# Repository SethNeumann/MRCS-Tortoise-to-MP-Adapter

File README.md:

# REPO NAME: MRCS-Tortoise-to-MP-Adapter

## License: Creative Commons Attribution-NonCommercial-ShareAlike

relay driven by a low power tortoise drive circuit (usually an LM324). Relay operates and switches 12V to MP Motor
eventually will have a 3.5mm phoenix plug for MP10

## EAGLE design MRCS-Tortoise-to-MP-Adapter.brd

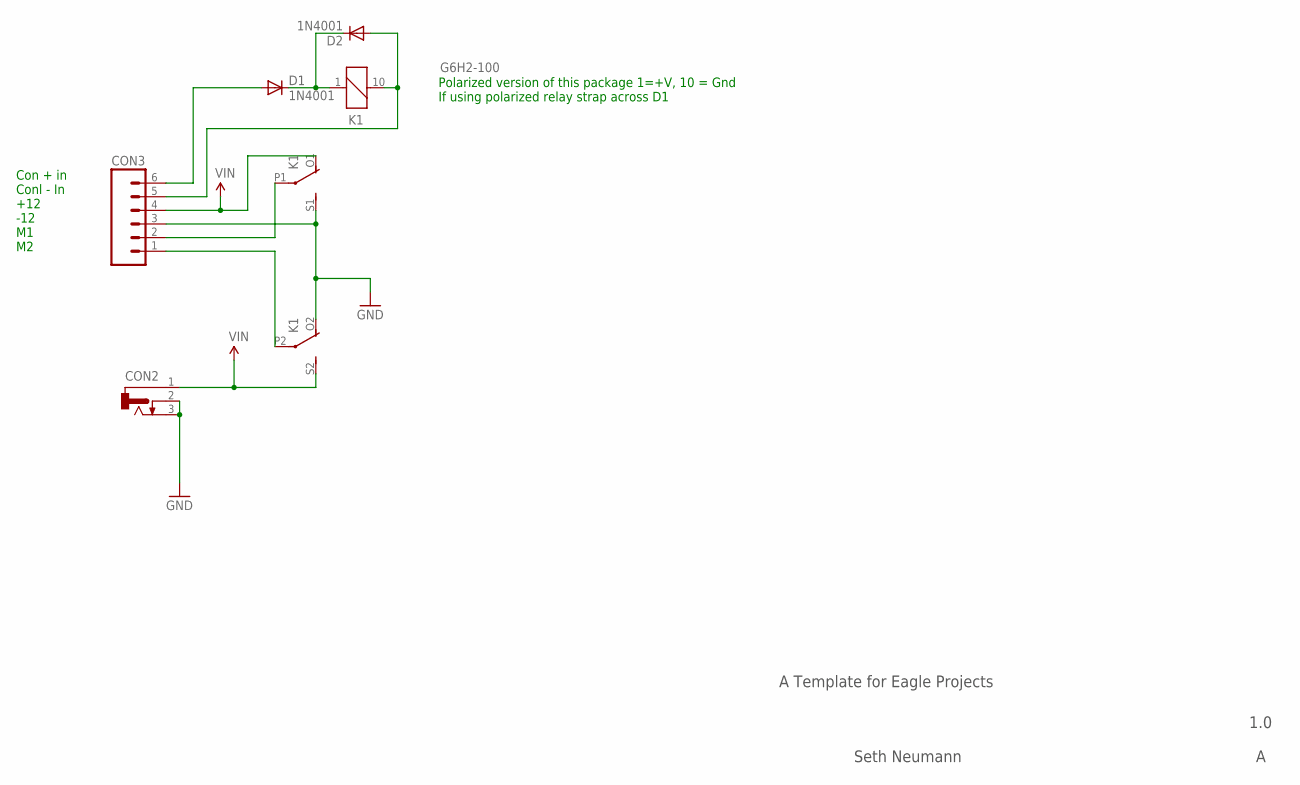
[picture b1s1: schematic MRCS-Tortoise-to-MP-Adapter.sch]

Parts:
CON2: CONNECTOR-DC-POWER-RA; DCJ0202
CON3: CONNECTOR-M063.5MM-6; SCREWTERMINAL-3.5MM-6
D1, D2: 1N4001; DIODE-1N4001
K1: G6H2-100

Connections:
GND: CON2.2, CON2.3, CON3.3, K1.O2 (O), K1.S1 (S)
unnamed: CON3.6, D1.A
unnamed: D1.C, D2.C, K1.1
unnamed: CON3.5, D2.A, K1.10 (2)
unnamed: CON3.2, K1.P1
unnamed: CON3.1, K1.P2
VIN: CON2.1, CON3.4, K1.O1 (O), K1.S2 (S)

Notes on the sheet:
A Template for Eagle Projects
1.0
Seth Neumann
Polarized version of this package 1=+V, 10 = Gnd If using polarized relay strap across D1
Con + in Conl - In +12 -12 M1 M2

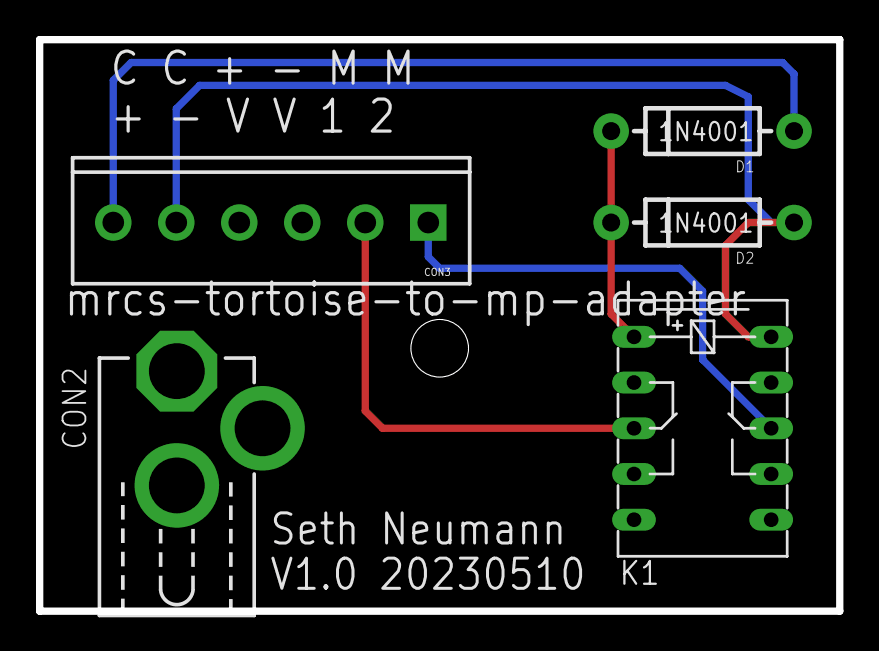
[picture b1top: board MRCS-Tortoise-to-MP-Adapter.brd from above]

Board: 2 copper layers, 44.5 x 31.8 mm, 8 parts (0 on the bottom side), 7 nets.

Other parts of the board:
U$1: MRCSLOGOTOP
U$2: CA-PROP65WARNING
U$3: MRCSLOGOBTM

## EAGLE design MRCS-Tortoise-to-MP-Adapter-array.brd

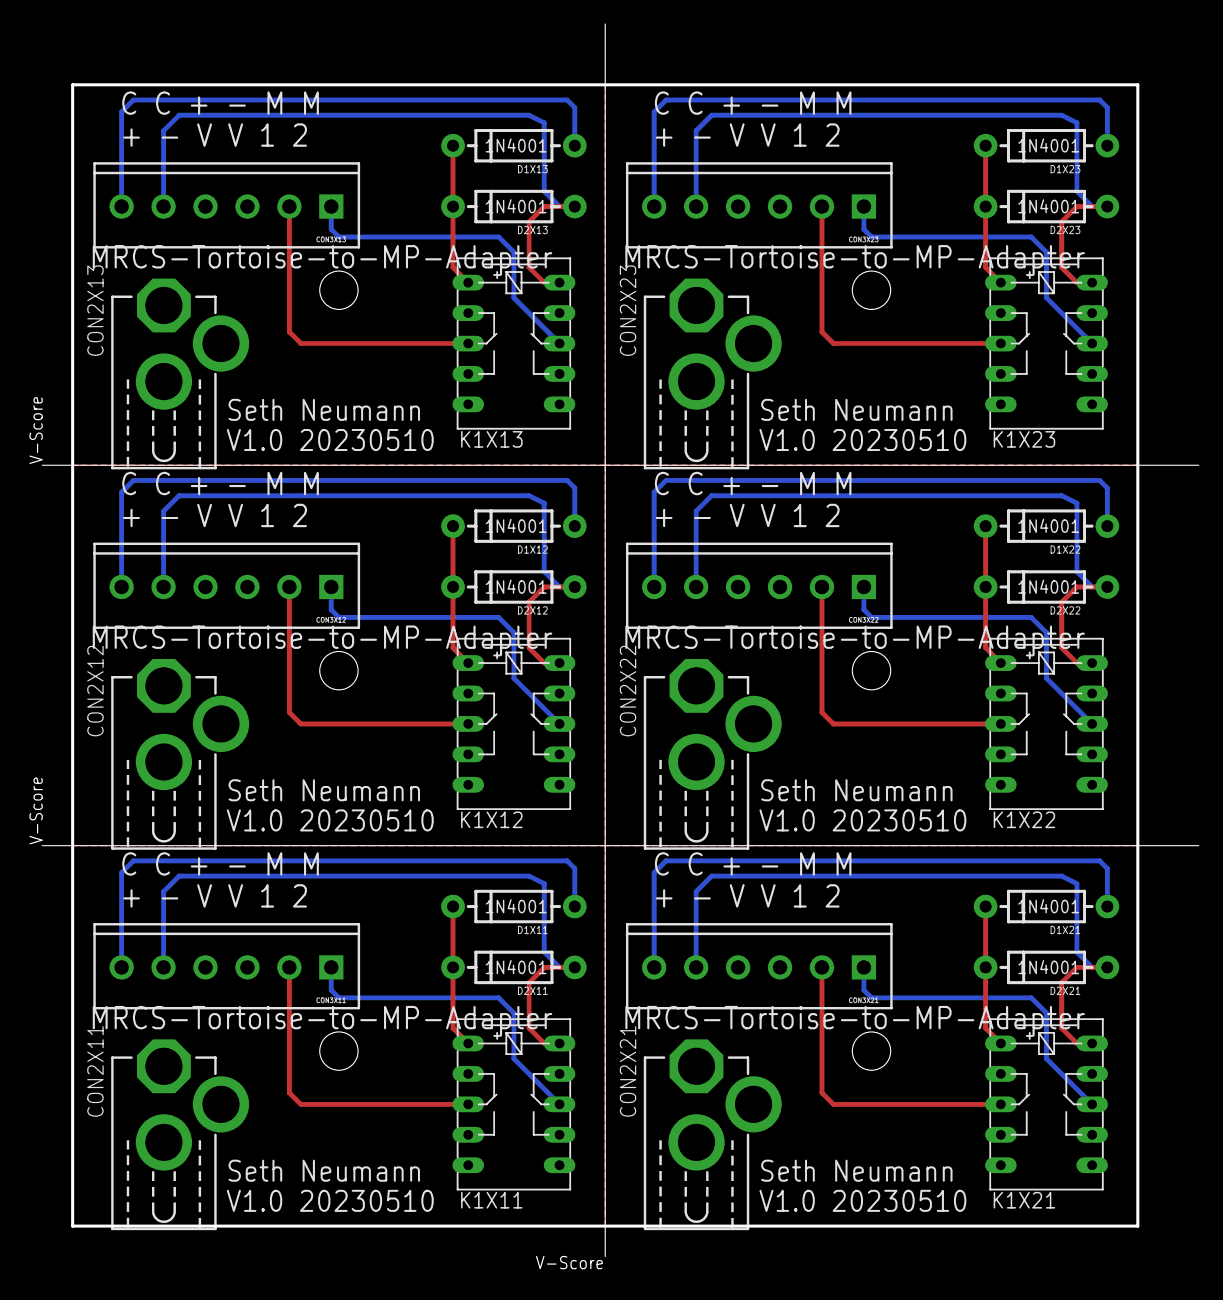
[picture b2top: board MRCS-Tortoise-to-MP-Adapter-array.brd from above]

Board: 2 copper layers, 97.8 x 104.2 mm, 48 parts (0 on the bottom side), 42 nets.

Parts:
CON2X11, CON2X12, CON2X13, CON2X21, CON2X22, CON2X23: DCJ0202
CON3X11, CON3X12, CON3X13, CON3X21, CON3X22, CON3X23: SCREWTERMINAL-3.5MM-6
D1X11, D1X12, D1X13, D1X21, D1X22, D1X23, D2X11, D2X12, D2X13, D2X21, D2X22, D2X23: 1N4001; DIODE-1N4001
K1X11, K1X12, K1X13, K1X21, K1X22, K1X23: G6H2-100
U$1X11, U$1X12, U$1X13, U$1X21, U$1X22, U$1X23: MRCSLOGOTOP
U$2X11, U$2X12, U$2X13, U$2X21, U$2X22, U$2X23: CA-PROP65WARNING
U$3X11, U$3X12, U$3X13, U$3X21, U$3X22, U$3X23: MRCSLOGOBTM

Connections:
GNDX11: CON2X11.2, CON2X11.3, CON3X11.3, K1X11.O2, K1X11.S1
GNDX12: CON2X12.2, CON2X12.3, CON3X12.3, K1X12.O2, K1X12.S1
GNDX13: CON2X13.2, CON2X13.3, CON3X13.3, K1X13.O2, K1X13.S1
GNDX21: CON2X21.2, CON2X21.3, CON3X21.3, K1X21.O2, K1X21.S1
GNDX22: CON2X22.2, CON2X22.3, CON3X22.3, K1X22.O2, K1X22.S1
GNDX23: CON2X23.2, CON2X23.3, CON3X23.3, K1X23.O2, K1X23.S1
unnamed: CON3X11.6, D1X11.A
unnamed: CON3X12.6, D1X12.A
unnamed: CON3X13.6, D1X13.A
unnamed: CON3X21.6, D1X21.A
unnamed: CON3X22.6, D1X22.A
unnamed: CON3X23.6, D1X23.A
unnamed: D1X11.C, D2X11.C, K1X11.1
unnamed: D1X12.C, D2X12.C, K1X12.1
unnamed: D1X13.C, D2X13.C, K1X13.1
unnamed: D1X21.C, D2X21.C, K1X21.1
unnamed: D1X22.C, D2X22.C, K1X22.1
unnamed: D1X23.C, D2X23.C, K1X23.1
unnamed: CON3X11.5, D2X11.A, K1X11.10
unnamed: CON3X12.5, D2X12.A, K1X12.10
unnamed: CON3X13.5, D2X13.A, K1X13.10
unnamed: CON3X21.5, D2X21.A, K1X21.10
unnamed: CON3X22.5, D2X22.A, K1X22.10
unnamed: CON3X23.5, D2X23.A, K1X23.10
unnamed: CON3X11.2, K1X11.P1
unnamed: CON3X12.2, K1X12.P1
unnamed: CON3X13.2, K1X13.P1
unnamed: CON3X21.2, K1X21.P1
unnamed: CON3X22.2, K1X22.P1
unnamed: CON3X23.2, K1X23.P1
unnamed: CON3X11.1, K1X11.P2
unnamed: CON3X12.1, K1X12.P2
unnamed: CON3X13.1, K1X13.P2
unnamed: CON3X21.1, K1X21.P2
unnamed: CON3X22.1, K1X22.P2
unnamed: CON3X23.1, K1X23.P2
VINX11: CON2X11.1, CON3X11.4, K1X11.O1, K1X11.S2
VINX12: CON2X12.1, CON3X12.4, K1X12.O1, K1X12.S2
VINX13: CON2X13.1, CON3X13.4, K1X13.O1, K1X13.S2
VINX21: CON2X21.1, CON3X21.4, K1X21.O1, K1X21.S2
VINX22: CON2X22.1, CON3X22.4, K1X22.O1, K1X22.S2
VINX23: CON2X23.1, CON3X23.4, K1X23.O1, K1X23.S2

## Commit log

2023-05-08 intiial commit
2023-05-09 setting up drawing
2023-05-31 clean up in preparation for panelization
    1st rev worked well and seems OK, add Prop 65 warning and minor label cleanup
2023-05-31 changed info file status
    added fab date, put in production
2023-06-01 First draft of Instructions
    this is a first pass. Eventually I'll add a list of compatible relays
2023-06-01 zip of Eagle files
2023-06-01 schematic and layout pdfs
2023-06-29 Changes to V1.1
    - Corrected minor fit issues on the SIN01 and BlackMagic librarye ntries
    - removed the F0/F1 ground jumpers on the PCR SIN-01 as it seems to want to be pulled up, but putting them up didn't change the Freq or voltage either. I left pads for F0/F1 in case SIN-01 documentat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
    - changed the orientation so the break out will fit better in 7CM Tyco track (discontinued, but I have a stash)
    - simplified routing where possible.
2023-06-29 Update DESCRIPTION
    made a 2x3 array
2023-06-29 Update INFO
    changed production date to July 2023

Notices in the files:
parts and their libraries:
SparkFun-Aesthetics: Licensing: CC v3.0 Share-Alike You are welcome to use this library for commercial purposes.
